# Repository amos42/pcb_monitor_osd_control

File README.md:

# Monitor OSD Control Board

---

[모니터 OSD 컨트롤 버튼 보드](monitor_osd_control/)
([README.md](monitor_osd_control/README.md))

---

[iPAD LCD용 OSD 컨트롤 버튼 보드](ipad_osd_control/)
([README.md](ipad_osd_control/README.md))

---

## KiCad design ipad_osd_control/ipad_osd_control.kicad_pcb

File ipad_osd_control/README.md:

# Monitor OSD Control Board (for iPAD LCD)

회로도

PCB 이미지

샘플 이미지

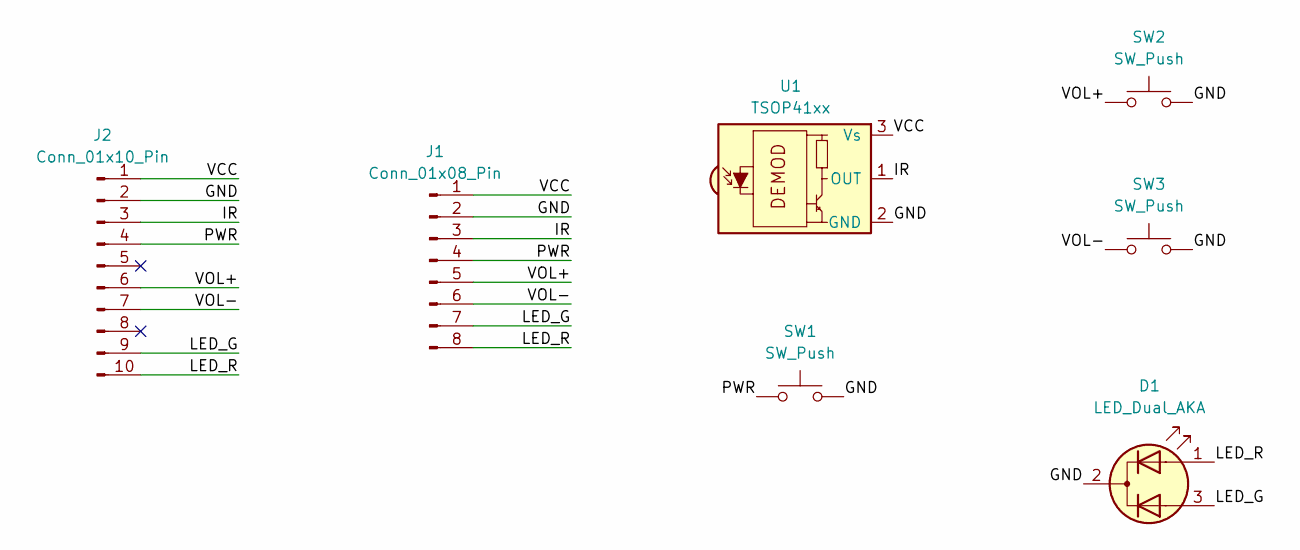
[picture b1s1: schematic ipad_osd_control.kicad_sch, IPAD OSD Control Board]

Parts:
D1: LED_Dual_AKA; LED_D3.0mm-3
J1: Conn_01x08_Pin; Molex_PicoBlade_53047-0810_1x08_P1.25mm_Vertical
J2: Conn_01x10_Pin; Molex_PicoBlade_53047-1010_1x10_P1.25mm_Vertical
SW1, SW2, SW3: SW_Push; SW_PUSH_6mm
U1: TSOP41xx; Vishay_MOLD-3Pin

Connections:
/GND: D1.2 (K), J1.2, J2.2, SW1.2, SW2.2, SW3.2, U1.2 (GND)
/IR: J1.3, J2.3, U1.1 (OUT)
/LED_G: D1.3 (A2), J1.7, J2.9
/LED_R: D1.1 (A1), J1.8, J2.10
/PWR: J1.4, J2.4, SW1.1
/VCC: J1.1, J2.1, U1.3 (Vs)
/VOL+: J1.5, J2.6, SW2.1
/VOL-: J1.6, J2.7, SW3.1

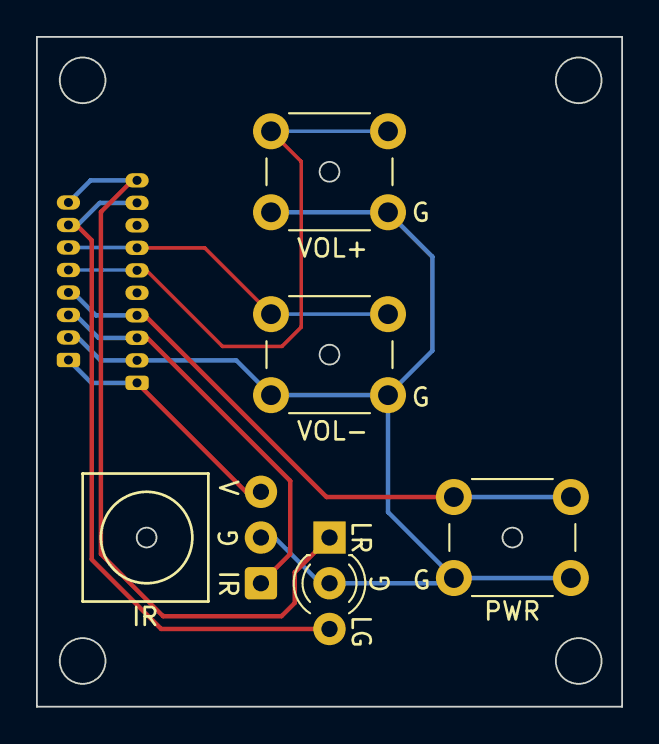
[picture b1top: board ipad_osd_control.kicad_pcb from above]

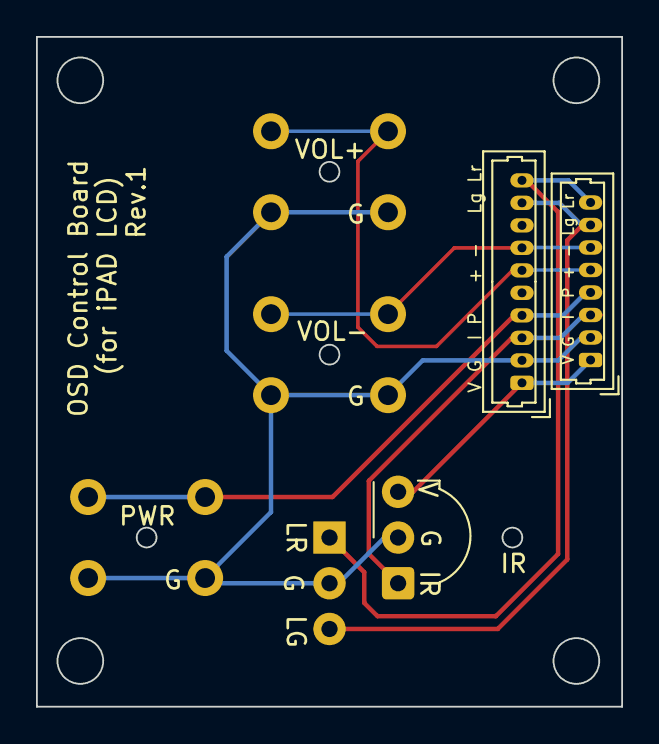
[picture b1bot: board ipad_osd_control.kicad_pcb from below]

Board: 2 copper layers, 32.5 x 37.2 mm, 7 parts (3 on the bottom side), 8 nets.

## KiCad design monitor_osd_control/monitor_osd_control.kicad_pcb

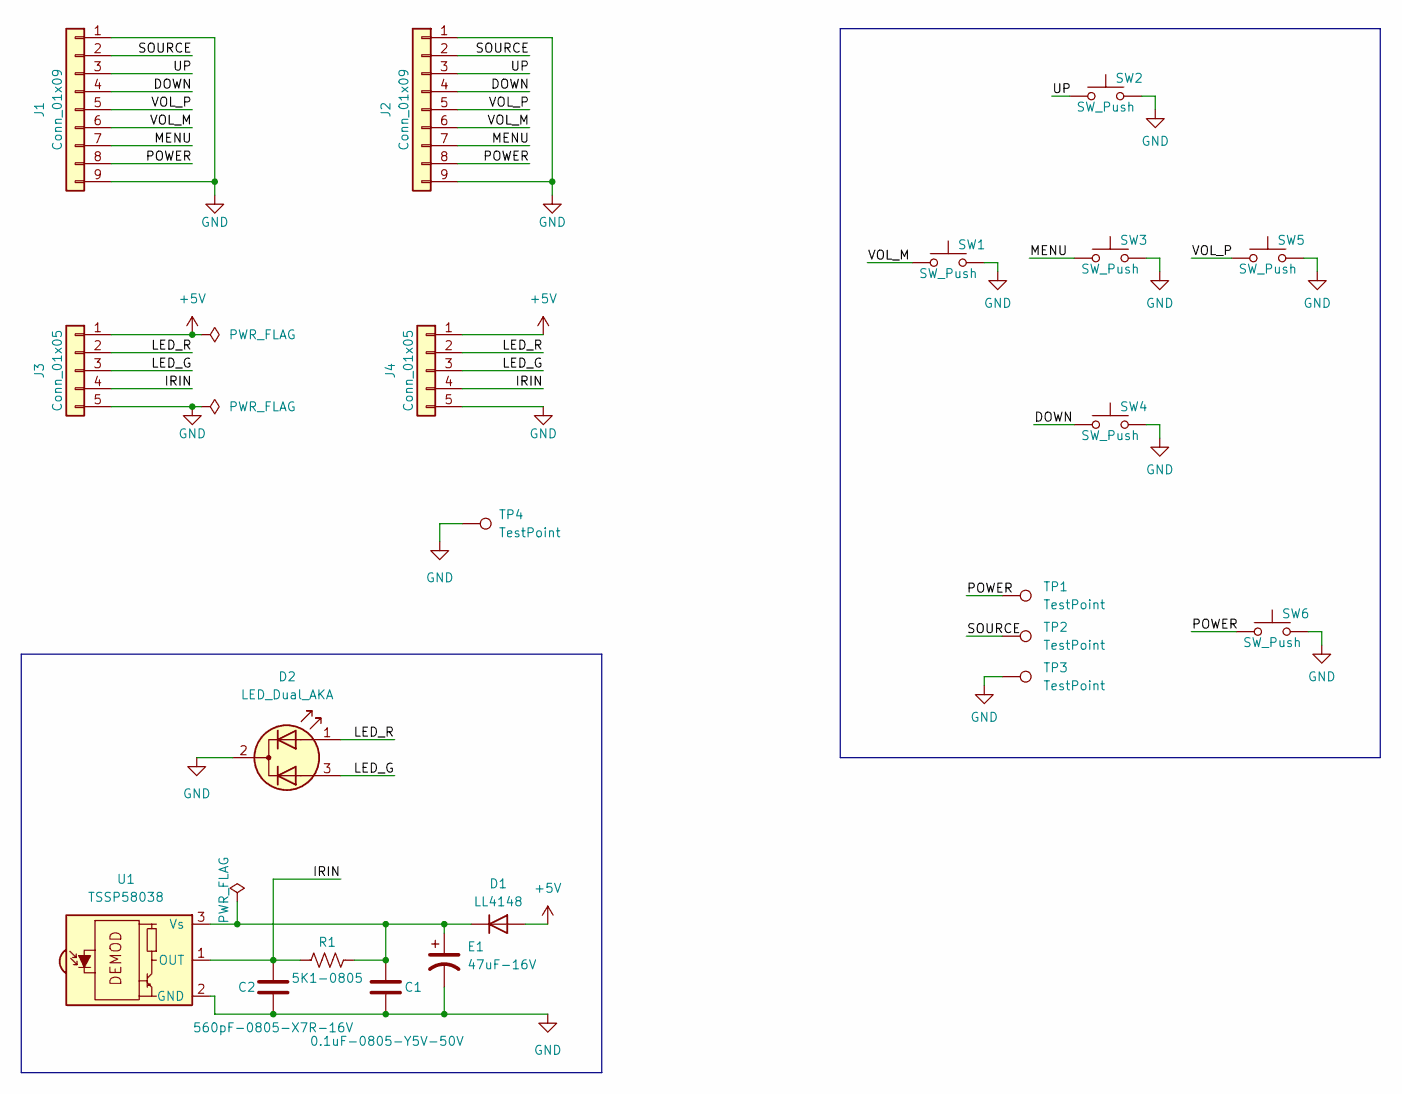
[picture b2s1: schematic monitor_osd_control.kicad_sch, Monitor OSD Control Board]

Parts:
C1: 0.1uF-0805-Y5V-50V; C_0805_2012Metric_Pad1.18x1.45mm_HandSolder
C2: 560pF-0805-X7R-16V; C_0805_2012Metric_Pad1.18x1.45mm_HandSolder
D1: LL4148; D_MiniMELF
D2: LED_Dual_AKA; LED_D3.0mm-3
E1: 47uF-16V; CP_Elec_5x5.4
J1: Conn_01x09; PinHeader_1x09_P2.00mm_Vertical
J2: Conn_01x09; PinHeader_1x09_P2.54mm_Vertical
J3: Conn_01x05; PinHeader_1x05_P2.00mm_Vertical
J4: Conn_01x05; PinHeader_1x05_P2.54mm_Vertical
R1: 5K1-0805; R_0805_2012Metric_Pad1.20x1.40mm_HandSolder
SW1, SW2, SW3, SW4, SW5: SW_Push; SW_PUSH-12mm_Complex
SW6: SW_Push; SW_PUSH_6mm
TP1, TP2, TP3: TestPoint; TestPoint_THTPad_D1.5mm_Drill0.7mm
TP4: TestPoint; TestPoint_THTPad_D2.0mm_Drill1.0mm
U1: TSSP58038; Vishay_MINICAST-3Pin

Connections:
+5V: D1.2 (A), J3.1, J4.1
/DOWN: J1.4, J2.4, SW4.1
/IRIN: C2.1, J3.4, J4.4, R1.1, U1.1 (OUT)
/LED_G: D2.3 (A2), J3.3, J4.3
/LED_R: D2.1 (A1), J3.2, J4.2
/MENU: J1.7, J2.7, SW3.1
/POWER: J1.8, J2.8, SW6.1, TP1.1
/SOURCE: J1.2, J2.2, TP2.1
/UP: J1.3, J2.3, SW2.1
/VOL_M: J1.6, J2.6, SW1.1
/VOL_P: J1.5, J2.5, SW5.1
GND: C1.2, C2.2, D2.2 (K), E1.2, J1.1, J1.9, J2.1, J2.9, J3.5, J4.5, SW1.2, SW2.2, SW3.2, SW4.2, SW5.2, SW6.2, TP3.1, TP4.1, U1.2 (GND)
unnamed: C1.1, D1.1 (K), E1.1, R1.2, U1.3 (Vs)

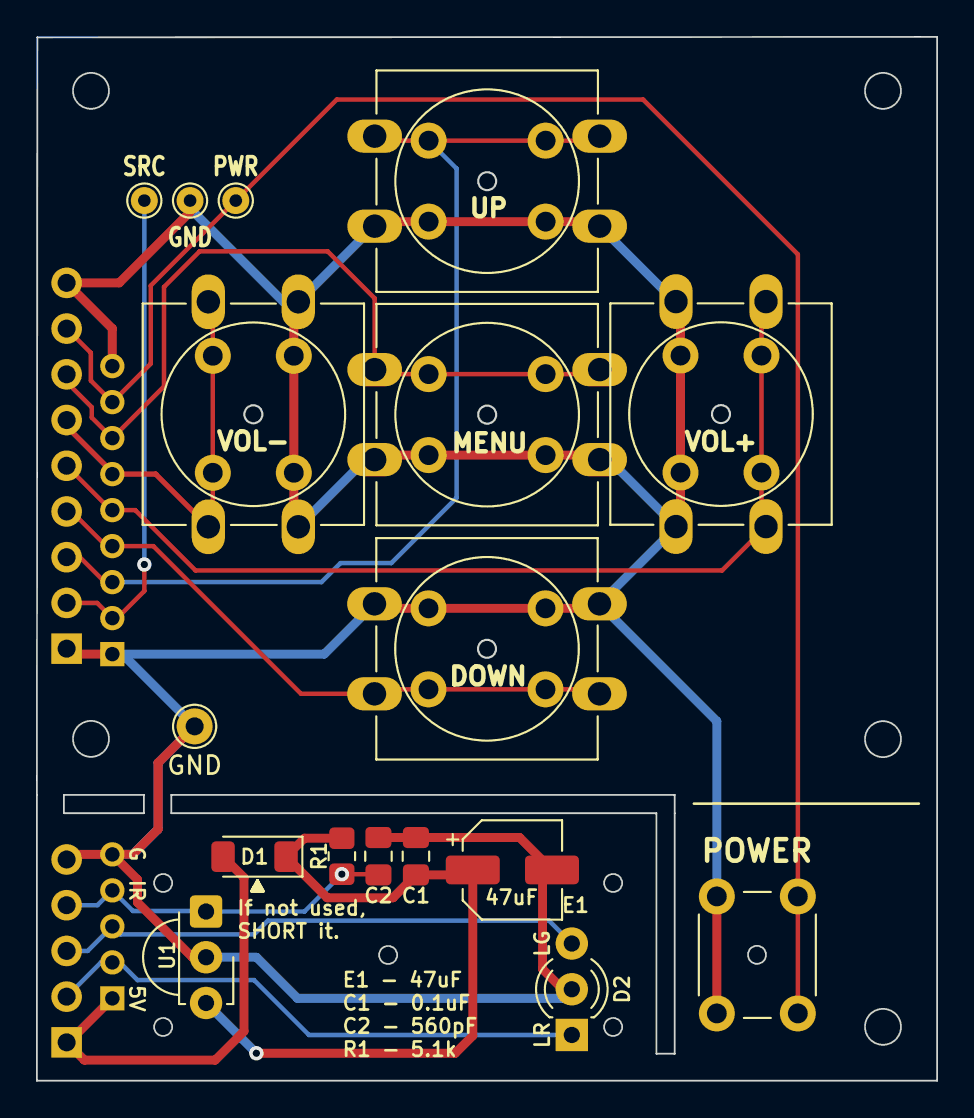
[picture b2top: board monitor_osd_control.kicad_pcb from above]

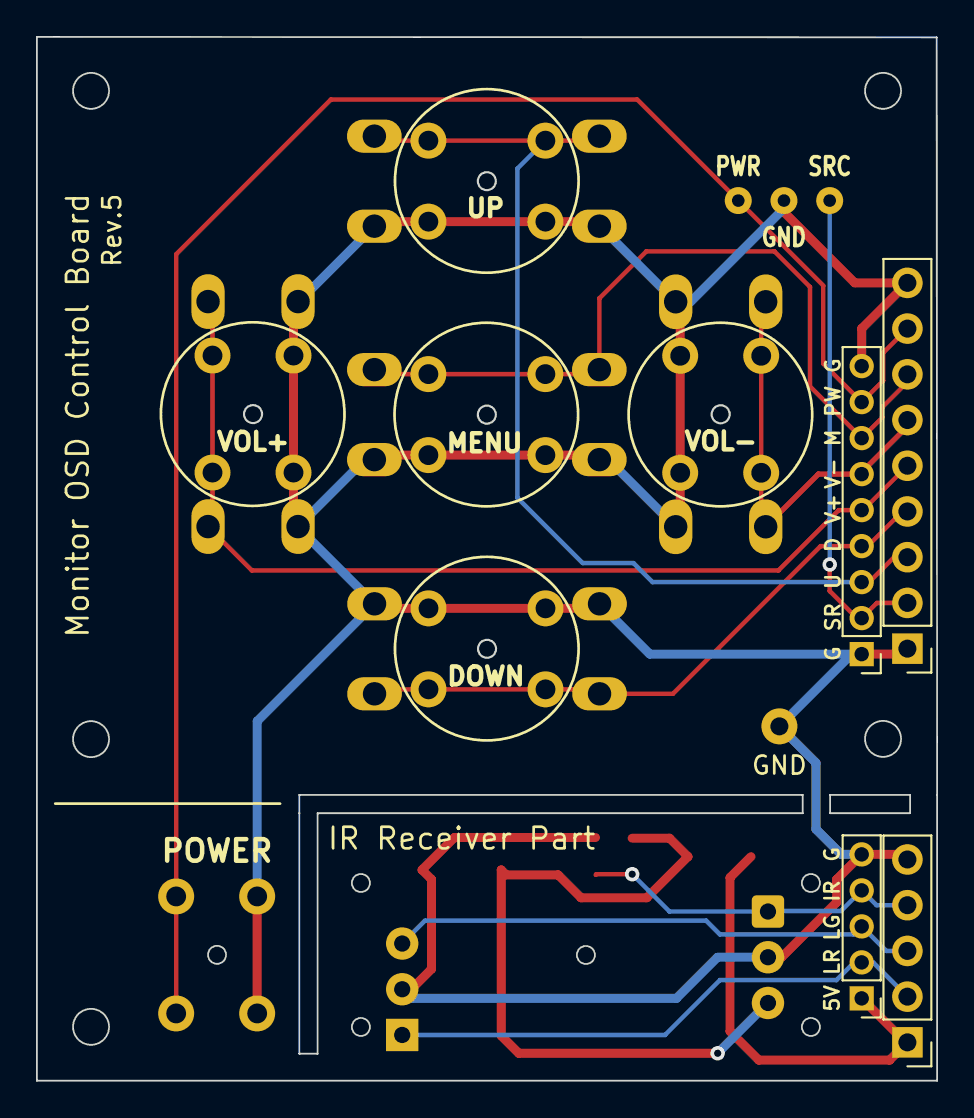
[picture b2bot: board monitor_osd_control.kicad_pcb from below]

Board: 2 copper layers, 50.0 x 58.0 mm, 21 parts (4 on the bottom side), 13 nets.

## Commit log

2023-02-12 배선 최적화 및 pretty 경로 보정
2023-03-11 커넥터 위치 미세하게 안쪽으로 조정
2023-03-11 gitignore 파일 추가
2023-03-26 버튼을 12mm와 6mm 겸용으로
2023-03-28 Rev 5로 업데이트
    - 버튼을 12mm 6mm 공용으로 사용 가능하도록 수정
    - 마우스 바이트 제거
2023-04-02 캐패시터 크기 변경
2023-04-02 GND 면적 증가
2023-12-18 ipad용 LCD OSD 컨트롤 보드 추가
